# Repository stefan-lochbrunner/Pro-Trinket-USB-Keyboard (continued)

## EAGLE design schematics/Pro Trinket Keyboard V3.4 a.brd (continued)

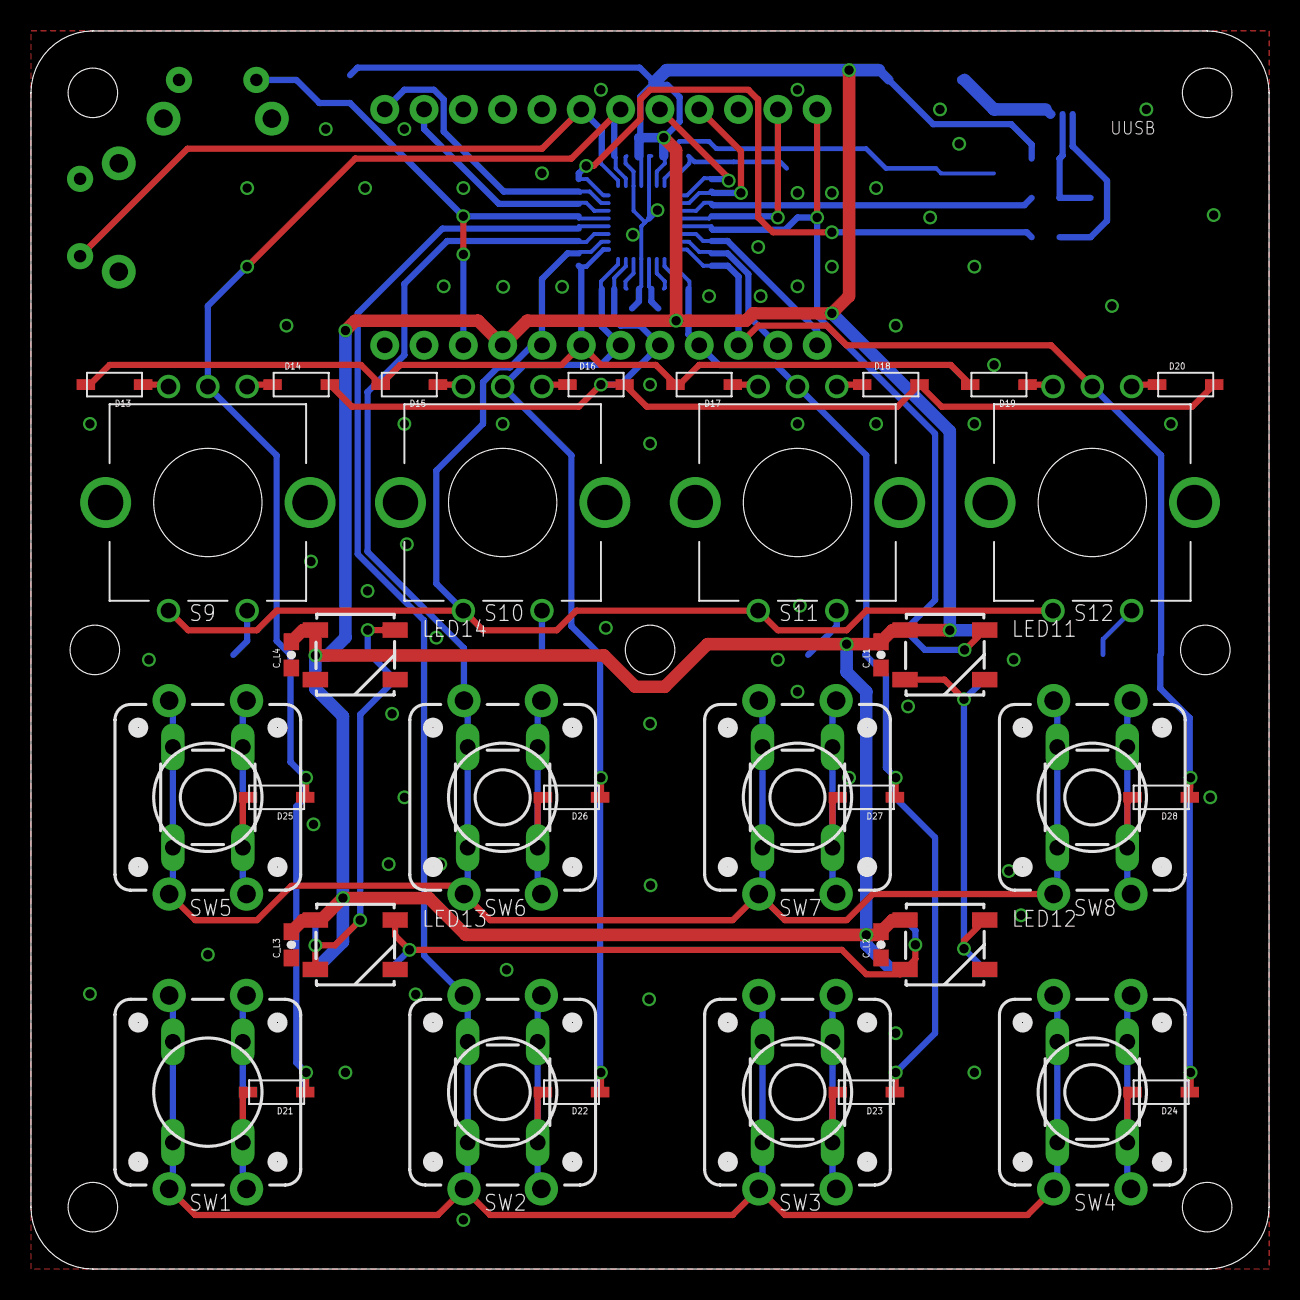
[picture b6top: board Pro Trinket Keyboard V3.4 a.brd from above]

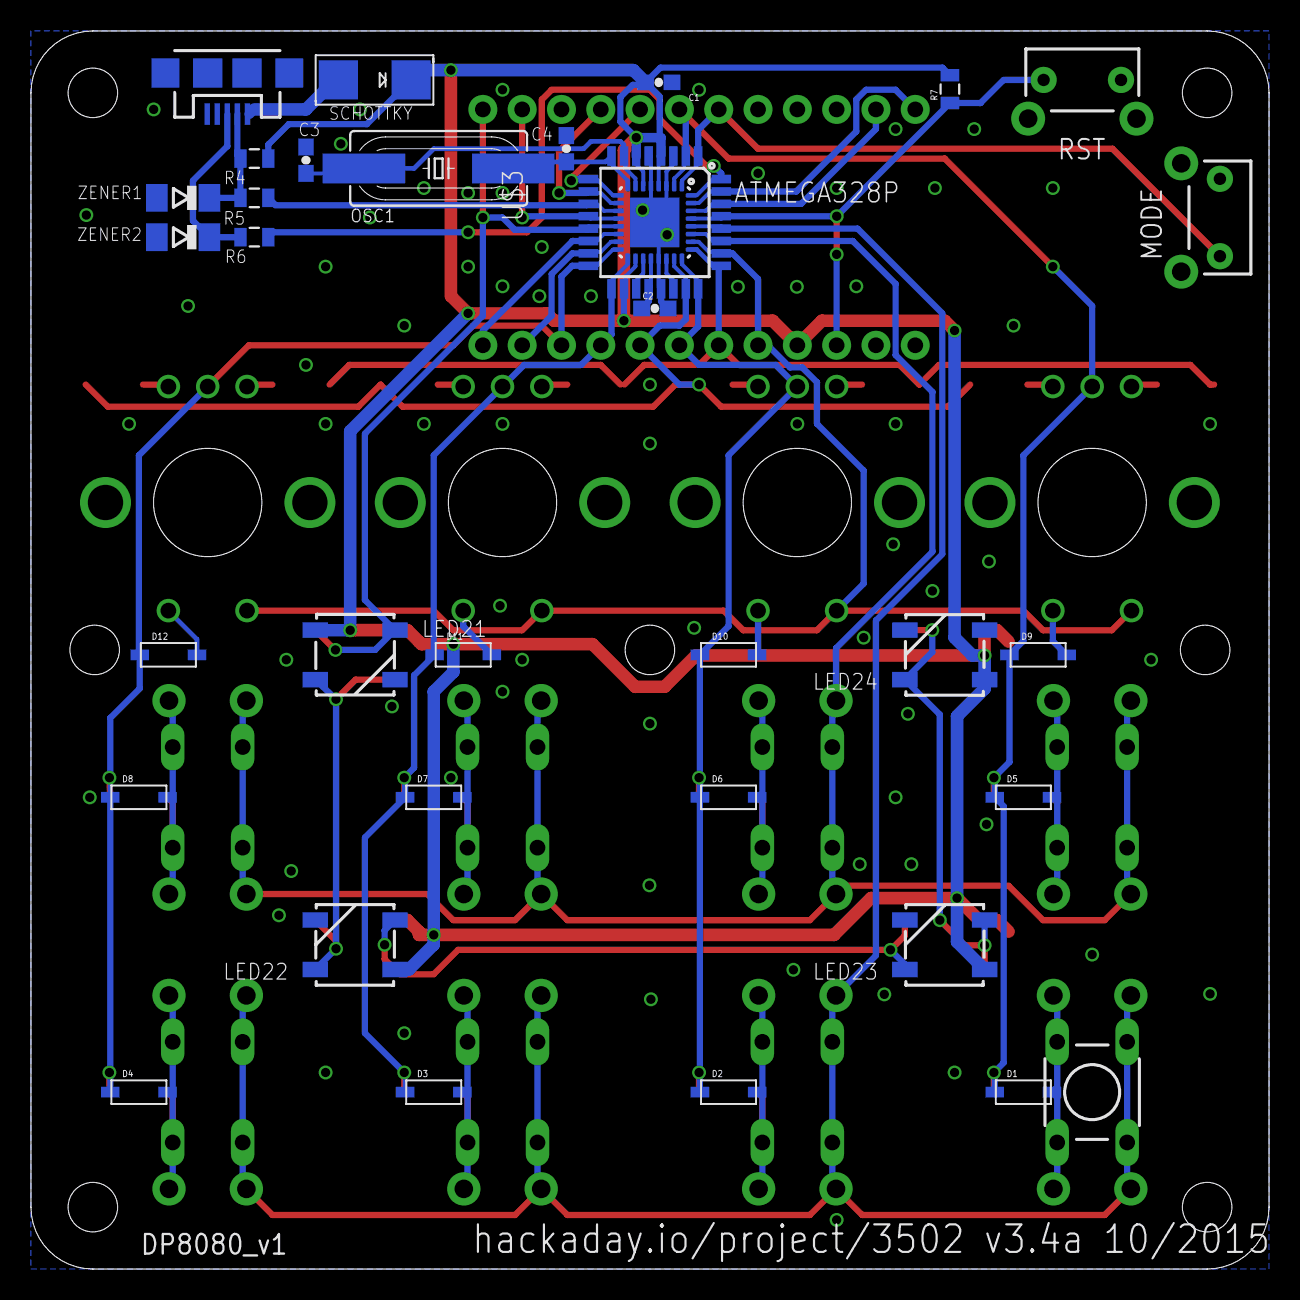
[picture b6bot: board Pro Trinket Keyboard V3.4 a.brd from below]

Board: 2 copper layers, 80.0 x 80.0 mm, 79 parts (35 on the bottom side), 54 nets.

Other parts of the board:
U$1: DP8080_V1

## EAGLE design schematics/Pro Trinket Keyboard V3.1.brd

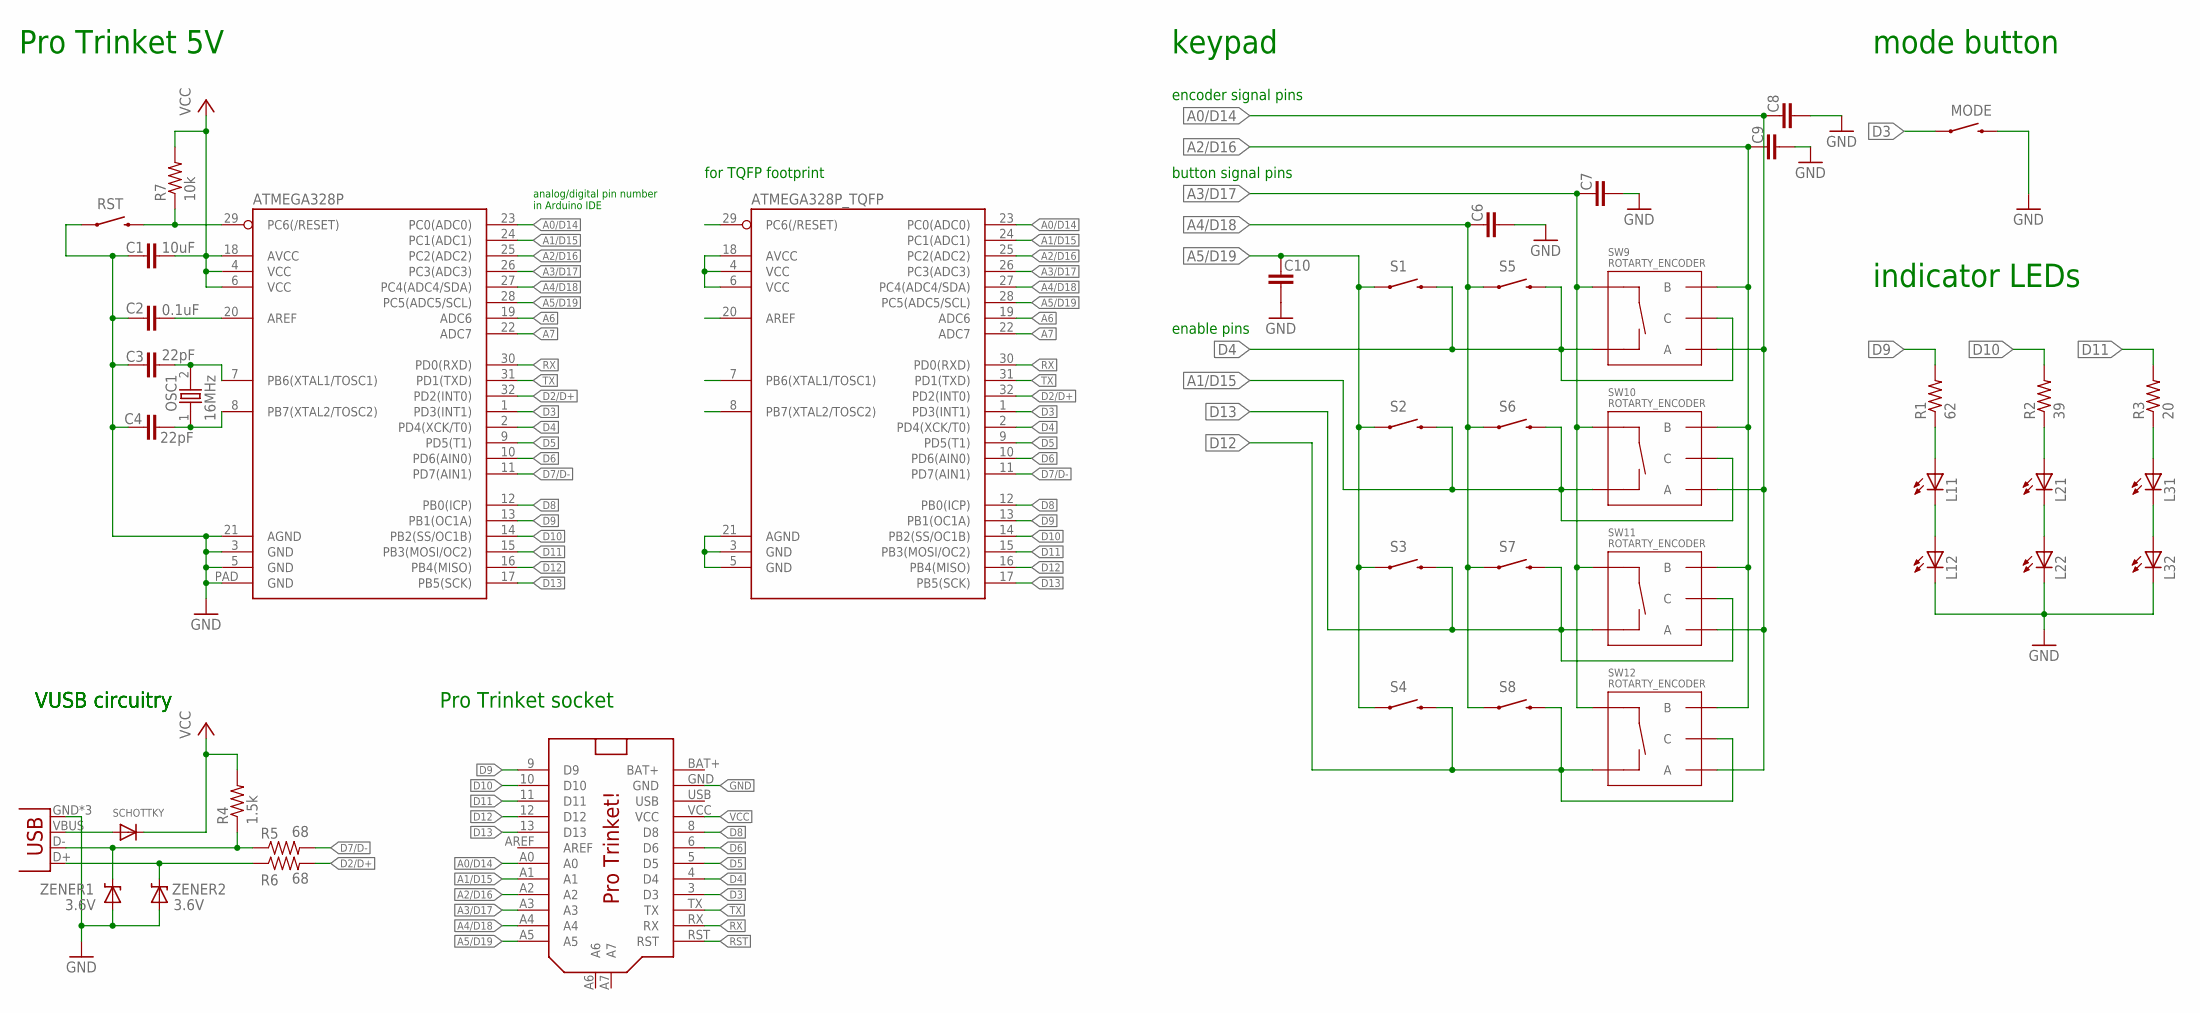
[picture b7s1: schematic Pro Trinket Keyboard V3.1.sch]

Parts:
ATMEGA328P: ATMEGA328P_MLFMLF32; MLF32-PAD
ATMEGA328P_TQFP: ATMEGA328P_TQFP; TQFP32-08
C1: 10uF; 0603-CAP
C2: 0.1uF; 0603-CAP
C3, C4: 22pF; 0603-CAP
C6, C7, C8, C9, C10: 22PF-50V-5%(0603); 0603-CAP
JP1: USB-MICROB
L11, L12, L21, L22, L31, L32: LEDCHIPLED_0805; CHIPLED_0805
MODE: SWITCH-MOMENTARY-2SIDE_EZ; TACTILE-PTH-SIDEEZ
OSC1: 16MHz; HC-49U
R1: 62; M0805
R2: 39; M0805
R3: 20; M0805
R4: 1.5k; 0805
R5, R6: 68; 0805
R7: 10k; 0805
RST: SWITCH-MOMENTARY-2SIDE_EZ; TACTILE-PTH-SIDEEZ
S1, S2, S3, S4, S5, S6, S7, S8: SWITCH-MOMENTARY-212MM; TACTILE-PTH-12MM
SCHOTTKY: DIODESMA; SMADIODE
SW9, SW10, SW11, SW12: ROTARTY_ENCODER; ROTARY_ENC_PLAIN
U$2: PRO_TRINKET; PROTRINKET
ZENER1, ZENER2: 3.6V; SOD-323

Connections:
A0/D14: ATMEGA328P.23 (PC0(ADC0)), ATMEGA328P_TQFP.23 (PC0(ADC0)), C8.1, SW9.A, SW10.A, SW11.A, SW12.A, U$2.A0
A1/D15: ATMEGA328P.24 (PC1(ADC1)), ATMEGA328P_TQFP.24 (PC1(ADC1)), S2.3 (2), S2.4 (2), S6.3 (2), S6.4 (2), SW10.C, SW10.SW-, U$2.A1
A2/D16: ATMEGA328P.25 (PC2(ADC2)), ATMEGA328P_TQFP.25 (PC2(ADC2)), C9.1, SW9.B, SW10.B, SW11.B, SW12.B, U$2.A2
A3/D17: ATMEGA328P.26 (PC3(ADC3)), ATMEGA328P_TQFP.26 (PC3(ADC3)), C7.1, SW9.SW+, SW10.SW+, SW11.SW+, SW12.SW+, U$2.A3
A4/D18: ATMEGA328P.27 (PC4(ADC4/SDA)), ATMEGA328P_TQFP.27 (PC4(ADC4/SDA)), C6.1, S5.1, S5.2 (1), S6.1, S6.2 (1), S7.1, S7.2 (1), S8.1, S8.2 (1), U$2.A4
A5/D19: ATMEGA328P.28 (PC5(ADC5/SCL)), ATMEGA328P_TQFP.28 (PC5(ADC5/SCL)), C10.1, S1.1, S1.2 (1), S2.1, S2.2 (1), S3.1, S3.2 (1), S4.1, S4.2 (1), U$2.A5
A6: ATMEGA328P.19 (ADC6), ATMEGA328P_TQFP.19 (ADC6)
A7: ATMEGA328P.22 (ADC7), ATMEGA328P_TQFP.22 (ADC7)
AREF: ATMEGA328P.20 (AREF), ATMEGA328P_TQFP.20 (AREF), C2.2
BAT+: U$2.BAT+
D2/D+: ATMEGA328P.32 (PD2(INT0)), ATMEGA328P_TQFP.32 (PD2(INT0)), R6.2
D3: ATMEGA328P.1 (PD3(INT1)), ATMEGA328P_TQFP.1 (PD3(INT1)), MODE.1, U$2.3 (D3)
D4: ATMEGA328P.2 (PD4(XCK/T0)), ATMEGA328P_TQFP.2 (PD4(XCK/T0)), S1.3 (2), S1.4 (2), S5.3 (2), S5.4 (2), SW9.C, SW9.SW-, U$2.4 (D4)
D5: ATMEGA328P.9 (PD5(T1)), ATMEGA328P_TQFP.9 (PD5(T1)), U$2.5 (D5)
D6: ATMEGA328P.10 (PD6(AIN0)), ATMEGA328P_TQFP.10 (PD6(AIN0)), U$2.6 (D6)
D7/D-: ATMEGA328P.11 (PD7(AIN1)), ATMEGA328P_TQFP.11 (PD7(AIN1)), R5.2
D8: ATMEGA328P.12 (PB0(ICP)), ATMEGA328P_TQFP.12 (PB0(ICP)), U$2.8 (D8)
D9: ATMEGA328P.13 (PB1(OC1A)), ATMEGA328P_TQFP.13 (PB1(OC1A)), R1.2, U$2.9 (D9)
D10: ATMEGA328P.14 (PB2(SS/OC1B)), ATMEGA328P_TQFP.14 (PB2(SS/OC1B)), R2.2, U$2.10 (D10)
D11: ATMEGA328P.15 (PB3(MOSI/OC2)), ATMEGA328P_TQFP.15 (PB3(MOSI/OC2)), R3.2, U$2.11 (D11)
D12: ATMEGA328P.16 (PB4(MISO)), ATMEGA328P_TQFP.16 (PB4(MISO)), S4.3 (2), S4.4 (2), S8.3 (2), S8.4 (2), SW12.C, SW12.SW-, U$2.12 (D12)
D13: ATMEGA328P.17 (PB5(SCK)), ATMEGA328P_TQFP.17 (PB5(SCK)), S3.3 (2), S3.4 (2), S7.3 (2), S7.4 (2), SW11.C, SW11.SW-, U$2.13 (D13)
GND: ATMEGA328P.3 (GND), ATMEGA328P.5 (GND), ATMEGA328P.21 (AGND), ATMEGA328P.PAD (GND), ATMEGA328P_TQFP.3 (GND), ATMEGA328P_TQFP.5 (GND), ATMEGA328P_TQFP.21 (AGND), C1.1, C2.1, C3.1, C4.2, C6.2, C7.2, C8.2, C9.2, C10.2, JP1.GND, JP1.MT1 (GND), JP1.MT2 (GND), L12.C, L22.C, L32.C, MODE.2, RST.1, U$2.GND, ZENER1.A, ZENER2.A
L31: L31.C, L32.A
unnamed: L11.A, R1.1
unnamed: L11.C, L12.A
unnamed: L21.A, R2.1
unnamed: L21.C, L22.A
unnamed: L31.A, R3.1
unnamed: JP1.VBUS, SCHOTTKY.A
unnamed: JP1.D-, R4.1, R5.1, ZENER1.C
unnamed: JP1.D+, R6.1, ZENER2.C
RST: ATMEGA328P.29 (PC6(/RESET)), ATMEGA328P_TQFP.29 (PC6(/RESET)), R7.1, RST.2, U$2.RST
RX: ATMEGA328P.30 (PD0(RXD)), ATMEGA328P_TQFP.30 (PD0(RXD)), U$2.RX
TX: ATMEGA328P.31 (PD1(TXD)), ATMEGA328P_TQFP.31 (PD1(TXD)), U$2.TX
USB: U$2.USB
VCC: ATMEGA328P.4 (VCC), ATMEGA328P.6 (VCC), ATMEGA328P.18 (AVCC), ATMEGA328P_TQFP.4 (VCC), ATMEGA328P_TQFP.6 (VCC), ATMEGA328P_TQFP.18 (AVCC), C1.2, R4.2, R7.2, SCHOTTKY.C, U$2.VCC
XTAL1: ATMEGA328P.7 (PB6(XTAL1/TOSC1)), ATMEGA328P_TQFP.7 (PB6(XTAL1/TOSC1)), C3.2, OSC1.2
XTAL2: ATMEGA328P.8 (PB7(XTAL2/TOSC2)), ATMEGA328P_TQFP.8 (PB7(XTAL2/TOSC2)), C4.1, OSC1.1

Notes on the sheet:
keypad
mode button
indicator LEDs
Pro Trinket 5V
analog/digital pin number in Arduino IDE
VUSB circuitry
Pro Trinket socket
enable pins
encoder signal pins
button signal pins
for TQFP footprint

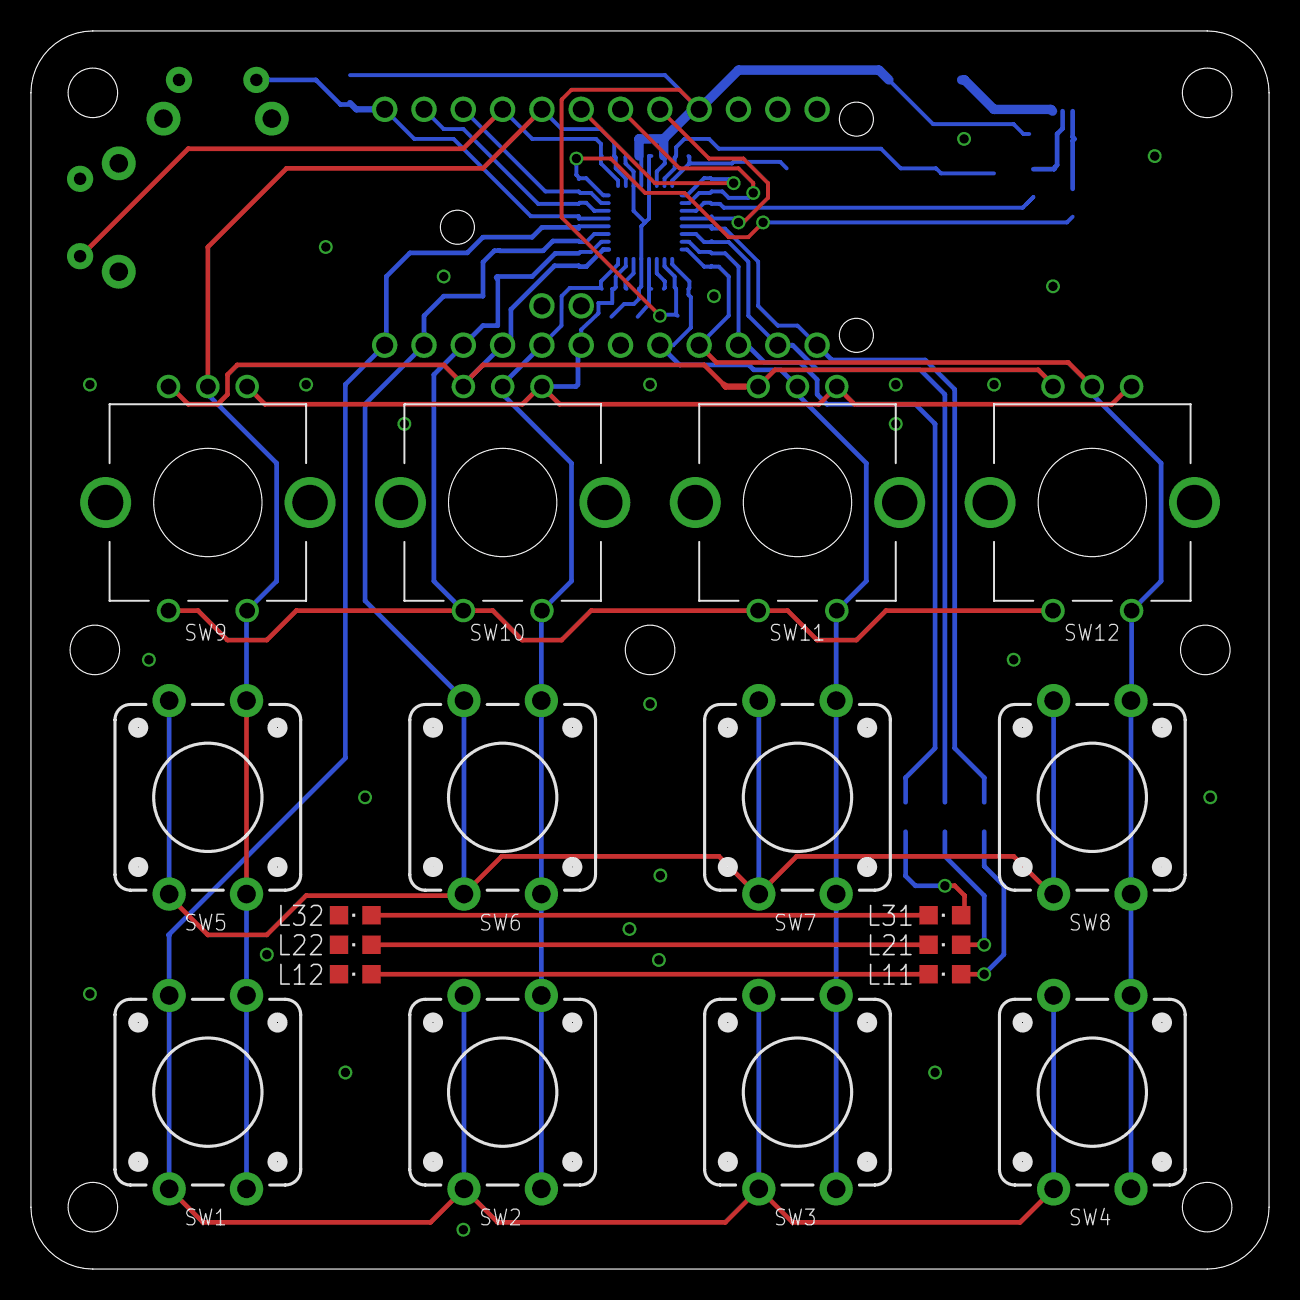
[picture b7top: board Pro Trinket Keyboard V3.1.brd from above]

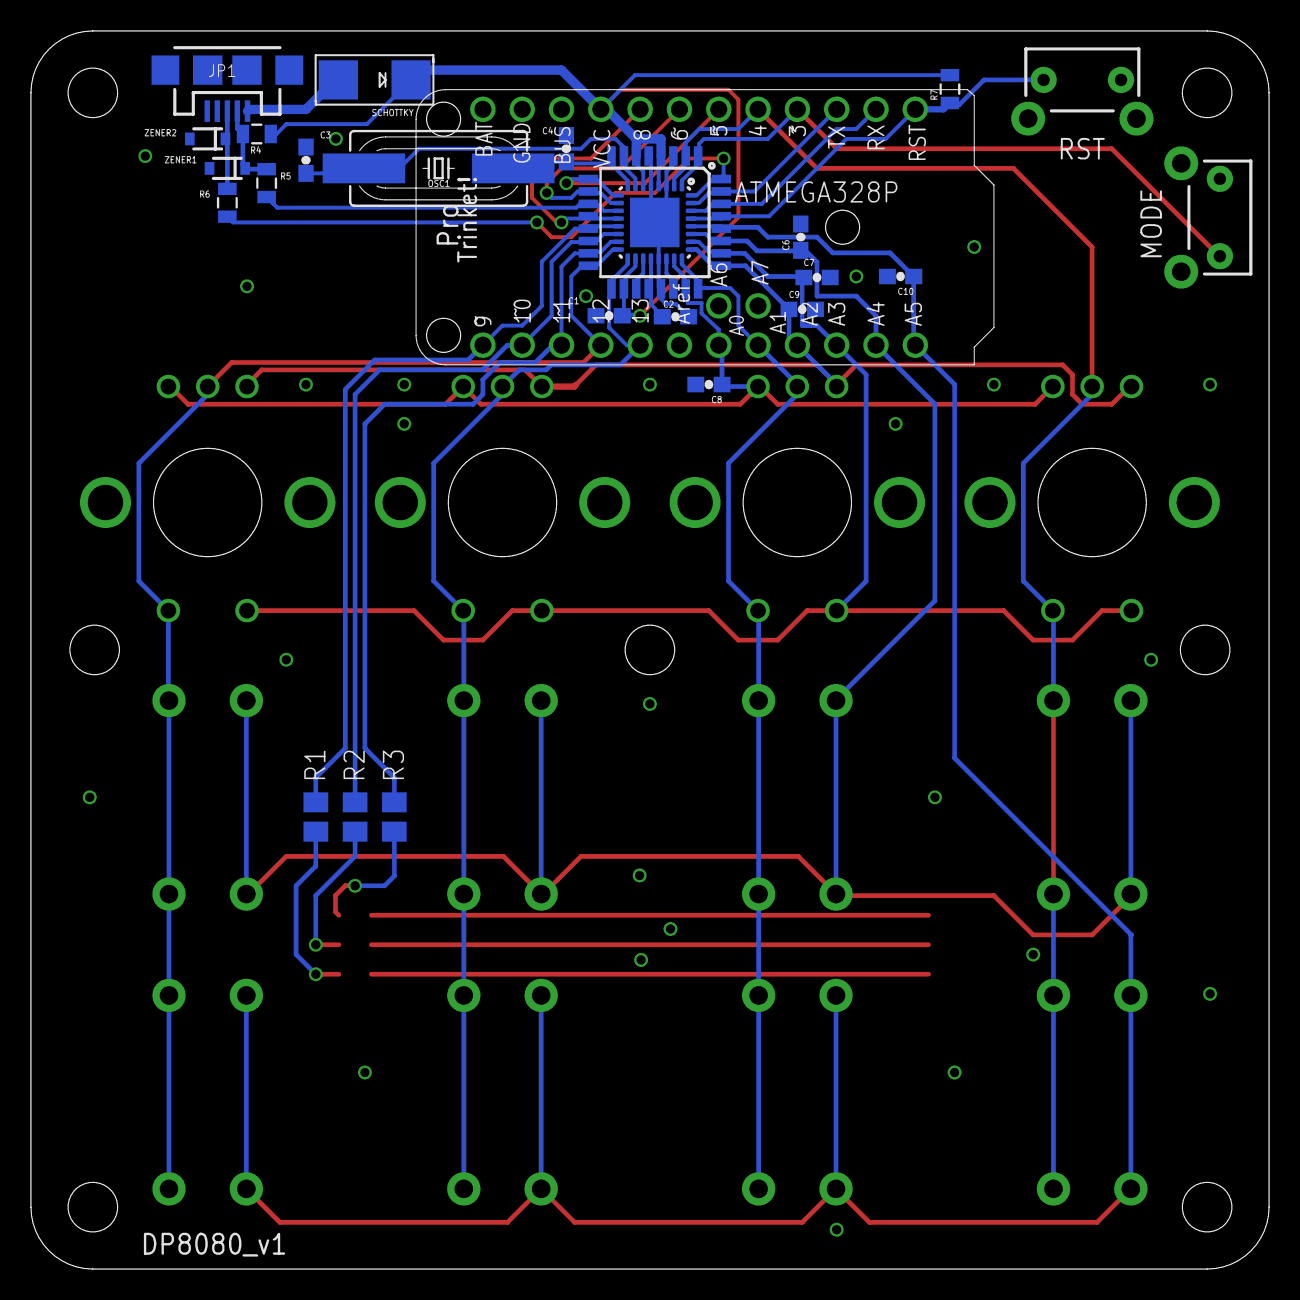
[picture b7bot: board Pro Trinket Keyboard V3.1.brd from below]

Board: 2 copper layers, 80.0 x 80.0 mm, 45 parts (26 on the bottom side), 37 nets.

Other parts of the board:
U$1: DP8080_V1

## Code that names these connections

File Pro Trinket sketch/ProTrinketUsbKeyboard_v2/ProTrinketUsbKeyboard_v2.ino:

/* 
Author: S.L.
11/2014 initial release
05/2015 updated for changed hardware

USB HID device to provide configrable keyboard shortcuts for 
various tasks (multimedia control, Photoshop,...)

Inteded for Adafruit Pro Trinket http://www.adafruit.com/product/2000
  PD2 / digital 2 is D+
  PD7 / digital 7 is D-
  PB5 / digital 13 has LED
Based on VUSB for Arduino https://code.google.com/p/vusb-for-arduino/
  PD5 / digital 5 used for D- pull-up

Notes:
- Originally intended to be used with keypad library
  http://playground.arduino.cc/code/Keypad
  but was abandoned because of conflicts in the usage of TIMSK0.
- Requires modificatonC:\Users\Steve\Downloads\Dropbox\Apps\arduino-1.0.5 of D- pull-up circuit to allow VUSB to disconnect and reconnect
  to be recognized as HID keyboard instead on USBtiny device.
  Manual switch added to select between pull-up to Vdd and connection to PD5 as outlined
  in usbconfig.h.
- See https://learn.adafruit.com/trinket-usb-volume-knob
  for instructions on rotary encoders
  
*/

//setup USB
#include "UsbKeyboard.h"

//kaypad & encoder definitions
int colPins[] = { 4, 15, 13, 12};  //select pins, driven LOW to select col => btn active LOW
int rowPins[] = {17, 18, 19};      //signal pins, read LOW means btn pressed
int encPins[] = {14, 16};          //encoder signal pins
int const rows = sizeof(rowPins)/sizeof(int);
int const cols = sizeof(colPins)/sizeof(int);

//array for prev btn states to detect distinct presses and releases
int key_prev[rows][cols] = {
  { 1, 1, 1, 1},
  { 1, 1, 1, 1},
  { 1, 1, 1, 1}
};
//array for prev encoder A pin state to detect rotation direction
int enc_prev[cols] = {
  1, 1, 1, 1
};

//misc UI definitions
int const modes = 3;    //number of modes/different keysets
int mode = 0;           //curent mode
//btn to toggle through modes
int modeBtn = 3;
int modeBtnPrev = 1;
//LEDs to indicate current mode
int ledPins[] = {11, 10, 9};
int leds = sizeof(ledPins)/sizeof(int);

//key sets for different modes
//usb codes for keypad buttons (4x3) in different modes (2) plus optional modifier
//see additional file for codes
int usb_codes[modes][rows][cols][2] = {
  //dialpad
  {
    {{30,0},{31,0},{32,0},{33,0}},
    {{34,0},{35,0},{36,0},{37,0}},
    {{38,0},{39,0},{10,0},{21,0}}
  },
  //multimedia
  {
    {{30,0},{31,0},{32,0},{33,0}},
    {{34,0},{35,0},{36,0},{37,0}},
    {{38,0},{10,0},{39,0},{21,0}}
  },
  //more keys
  {
    {{11,0},{ 8,0},{15,0},{18,0}},
    {{ 4,0},{ 6,0},{14,0},{ 7,0}},
    {{29,0},{10,0},{39,0},{44,0}}
  }
};
//encoder actions. 1 enc per col, cw & ccw direction (2) plus optional modifier (2)
int usb_codes_enc[modes][cols][2][2] = {
  //dialpad
  {
    {{81, 0},{82, 0}},
    {{30, 0},{31, 0}},
    {{30, 0},{31, 0}},
    {{30, 0},{31, 0}}
  },
  //multimedia
  {
    {{81, 0},{82, 0}},
    {{81, 0},{82, 0}},
    {{81, 0},{82, 0}},
    {{81, 0},{82, 0}}
  },
  //misc
  {
    {{81, 0},{82, 0}},
    {{81, 0},{82, 0}},
    {{81, 0},{82, 0}},
    {{81, 0},{82, 0}}
  }
};

void setup(){
  //set data direction for keypad
  //cols: select, drive low to select
  for(int i=0; i<cols; i++){
    pinMode(colPins[i], OUTPUT);
    digitalWrite(colPins[i], HIGH);
  }
  //rows: sense/read, active low
  for(int i=0; i<rows; i++){
    pinMode(rowPins[i], INPUT_PULLUP);
  }
  //set up encoder inputs
  pinMode(encPins[0], INPUT_PULLUP);
  pinMode(encPins[1], INPUT_PULLUP);
  //mode btn
  pinMode(modeBtn, INPUT_PULLUP);
  //mode LEDs
  for(int i=0; i<leds; i++){
    pinMode(ledPins[i], OUTPUT);
    digitalWrite(ledPins[i], HIGH);
    delayMs(200);
    digitalWrite(ledPins[i], LOW);
  }
  digitalWrite(ledPins[mode], HIGH);
  
  
  //USB
  TIMSK0&=!(1<<TOIE0);
  // Clear interrupts while performing time-critical operations
  cli();
  // Force re-enumeration so the host will detect us
  usbDeviceDisconnect();
  delayMs(250);
  usbDeviceConnect();
  // Set interrupts again
  sei();
  
}

void loop(){
  //Poll USB
  UsbKeyboard.update();
  
  //break criteria for while loop (to service USB)
  int count = 0;
  //poll inputs
  while(count < 100){
    count ++;
    
    //poll mode button
    if(digitalRead(modeBtn) == 0 && modeBtnPrev == 1){
      modeBtnPrev = 0;
      mode += 1;
      if(mode >= modes){
        mode = 0;
      }
      //change LEDs
      //turn off all LEDs
      for(int i=0; i<leds; i++){
        digitalWrite(ledPins[i], LOW);
      }
      //turn on current LED
      digitalWrite(ledPins[mode], HIGH);
    }
    else if (digitalRead(modeBtn) == 1 && modeBtnPrev == 0){
      modeBtnPrev = 1;
    }
    
    //cycle through cols
    for(int i=0; i<cols; i++){
      //enable col (active low)
      digitalWrite(colPins[i], LOW);

      //poll rows
      for(int j=0; j<rows; j++){
        //read state of current btn
        int but = digitalRead(rowPins[j]);    //Button Under Test
        
        //btn was just pressed (0), which means prev state was 1 (unpressed)
        if(but == 0 && key_prev[j][i] == 1){
          //set new prev state
          key_prev[j][i] = 0;
          
          //execute keystroke
          UsbKeyboard.sendKeyStroke(usb_codes[mode][j][i][0]);
        }
        //key release
        else if(but == 1 && key_prev[j][i] == 0){
          //set new prev state
          key_prev[j][i] = 1;
        }
      }
      // /poll rows

      //poll encoder
      int A = digitalRead(encPins[0]);
      int B = digitalRead(encPins[1]);
      //detect rotation
      if(A == 0 && enc_prev[i] == 1){
        //change prev state
        enc_prev[i] = 0;
        
        //determine rotation direction (cw/ccw)
        if(B == 1){
          //cw rotation ...orwhatever? 
          
          //execute keystroke
          UsbKeyboard.sendKeyStroke(usb_codes_enc[mode][i][0][0]);
        }
        else if(B == 0){
          //ccw rotation ...orwhatever?
          
          //execute keystroke
          UsbKeyboard.sendKeyStroke(usb_codes_enc[mode][i][1][0]);
        }
      }
      else if(A == 1 && B == 1){
        //no input on encoder pins
        enc_prev[i] = 1;
      }
      // /poll encoder

      //disable col
      digitalWrite(colPins[i], HIGH);
      
      delayMicroseconds(250);    //software debounce
    }
    // /cycle through cols
  }
}

void delayMs(unsigned int ms){
  for (int i = 0; i < ms; i++) {
    delayMicroseconds(1000);
  }
}

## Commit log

2015-01-01 added sketch and schematics
2015-01-01 added schematics image
2015-01-16 added V2 schematic w/ more details
2015-01-16 added V2 schematic image
2015-01-22 updated sketch to use defined modifiers
2015-01-22 Corrections in sketch comments, added keycodes.txt
    Added keycodes.txt which contains a collection of codes
2015-02-15 updated schematic, added layout
2015-02-16 added schematic and layout images
2015-02-16 changed filename
2015-03-28 updated schematic and layout
2015-03-29 added case templates
2015-05-09 added updated sketch for new hardware
2015-05-09 updated v2 sketch
    added startup animation
2015-05-14 updated v2 sketch
2015-05-23 gitignore
2015-06-02 added v3 sketch
2015-06-02 updated v3 sketch
2015-09-26 added v3.3 schematics & board
2015-09-26 updated v3.3 brd image
2015-09-26 added v3.2 schematic & board
2015-09-26 added v4 sketch & txt file w/ sorted keycodes
2015-09-27 updated v4 sketch
2015-10-20 added v3.4 schematics & board
2015-10-20 updated board file
2015-10-29 added v3.4 a schematic & board
2015-10-29 updated board files
2015-10-30 added v3.4a gerbers
2015-10-30 updated gerbers
2015-11-30 added v4 schematics
2015-11-30 initial Pro Trinket/Micro Keyboard Jr release
2015-12-05 added v4.1 schematics & board
2015-12-08 renamed v4
2015-12-08 added v4.2 schematics & board
2015-12-10 removed erroneous hardware versions
2015-12-10 restructured repo
2015-12-10 re-restructured repo
2015-12-11 added accessory boards
2015-12-12 added ProMicroKeyboard_dev
2015-12-12 updated ProMicroKeyboard_dev.ino
